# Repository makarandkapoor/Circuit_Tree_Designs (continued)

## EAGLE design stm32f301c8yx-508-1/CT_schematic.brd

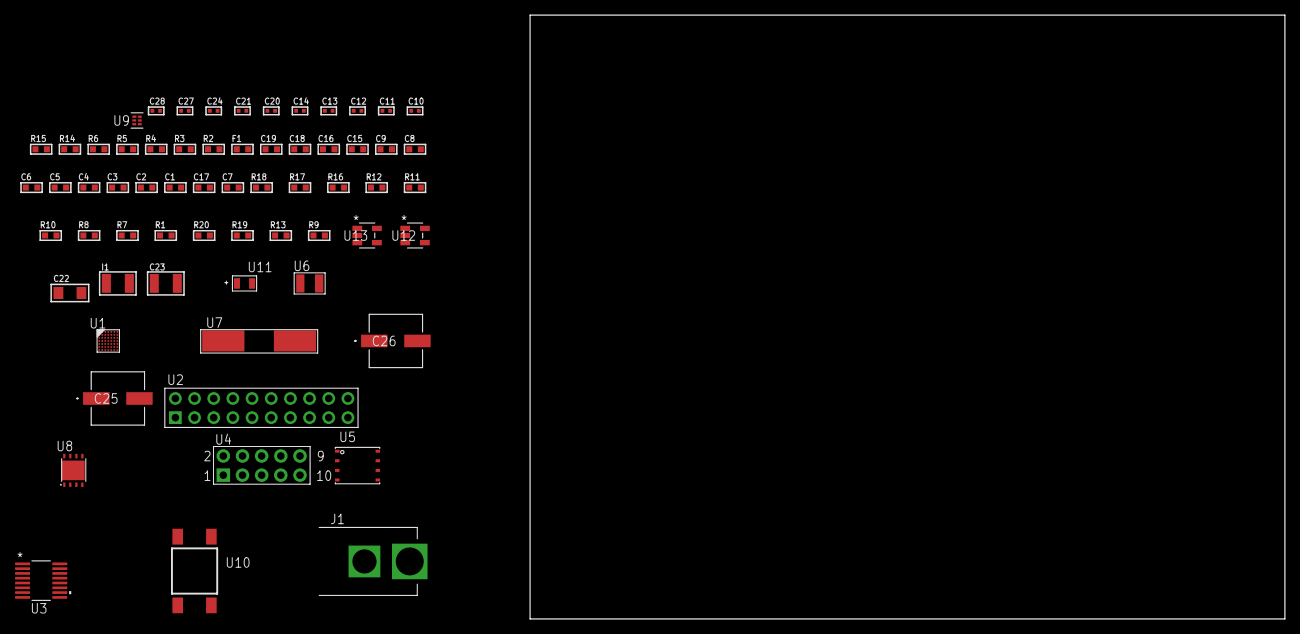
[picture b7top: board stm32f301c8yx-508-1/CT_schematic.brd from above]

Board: 2 copper layers, 100.0 x 80.0 mm, 64 parts (0 on the bottom side), 41 nets, no tracks yet.

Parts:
C1, C9, C15, C16, C18, C19: 1e-06; C0603
C2, C3, C4, C5, C6: 1e-07; C0603
C7: 4.7e-06; C0603
C8: 1e-08; C0603
C10, C11, C12, C13: 1e-11; C0402
C14, C24: 1e-07; C0402
C17: 2.2e-07; C0603
C20, C21, C27, C28: 1e-08; C0402
C22: 1e-05; C1206
C23: 1e-05; C1210
C25, C26: 0.0001; EXV-9H
F1: 240.0; L0603
I1: 1e-05; L1210
J1: PJ-037B; PJ-037B_PACKAGE
R1, R7, R8, R10, R11, R12, R16, R17: 10000.0; R0603
R2, R15: 1000.0; R0603
R3: 1270.0; R0603
R4: 4700.0; R0603
R5, R6: 2200.0; R0603
R9, R13: 100000.0; R0603
R14: 1500.0; R0603
R18: 18000.0; R0603
R19: 470000.0; R0603
R20: 120000.0; R0603
U1: STM32F301C8Y6; WLCSP49
U2: TST-110-05-T-D-RA
U3: LTC2804CGN-1#PBF; SSOP-16
U4: HTSS-105-01-G-D
U5: 24AA256-I/MF; DFN8-S
U6: ABS07-32.768KHZ-7-T
U7: ABLS-25.000MHZ-B2F-T
U8: LP3878SDX-ADJ/NOPB; WSON-8
U9: TPS3895ADRYR; SON-6
U10: 4-1437565-2; SW_4-1437565-2
U11: Q65110A2395; LGM67K-G1J2-24-Z
U12, U13: nc7sz125m5x; NC7SZ125M5X

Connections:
CLK_CRYSTAL_U1_C6: C10.1, U1.C6, U6.1
CLK_CRYSTAL_U1_C7: C11.1, U1.C7, U6.2
CLK_CRYSTAL_U1_D6: C12.1, U1.D6, U7.1
CLK_CRYSTAL_U1_D7: C13.1, U1.D7, U7.2
GND: C1.2, C2.2, C3.2, C4.2, C5.2, C6.2, C7.2, C8.2, C9.2, C10.2, C11.2, C12.2, C13.2, C14.2, C15.2, C16.2, C18.2, C19.2, C20.2, C21.2, C22.2, C23.2, C24.2, C25.2, C26.2, C27.2, C28.2, J1.2, R2.2, R7.2, R15.2, R18.2, R20.2, U1.B1, U1.D3, U1.E6, U1.F7, U2.4, U2.6, U2.8, U2.10, U2.12, U2.14, U2.16, U2.18, U2.20, U3.8, U4.9, U5.4, U8.3, U8.PAD, U9.2, U11.C, U12.2, U12.3, U13.1, U13.3
NET_U1_A2: R5.1, U1.A2, U5.6
NET_U1_A5: R7.1, U1.A5
NET_U1_A6: C8.1, C9.1, F1.1, U1.A6
NET_U1_C5: R6.1, U1.C5, U5.5
NET_U1_E7: R4.1, U1.E7, U13.4
NET_U1_G6: R3.1, U1.G6, U11.A
NET_U1_G7: R1.1, U1.G7, U10.3, U10.4
NET_U3_6: C15.1, U3.6
NET_U3_7: C17.1, I1.2, U3.7
NET_U3_9: C16.1, U3.9
NET_U3_10: C17.2, U3.10
NET_U3_11: R9.1, U3.11
NET_U4_3: U3.1, U4.3
NET_U4_4: U3.2, U4.4
NET_U4_5: U3.3, U4.5
NET_U4_6: U3.4, U4.6
NET_U5_1: R10.1, U5.1
NET_U5_2: R11.1, U5.2
NET_U5_3: R12.1, U5.3
NET_U8_1: C21.1, U8.1
NET_U8_6: R14.2, R15.1, U8.6
NET_U8_8: R13.1, U8.8
NET_U9_1: R17.1, R18.1, U9.1
NET_U9_3: R19.2, R20.1, U9.3
NET_U9_4: R16.1, U9.4, U12.4, U13.2
NET_U10_1: R2.1, U10.1, U10.2
PROC_SYS_JTCK_SWCLK: U1.A1, U2.9
PROC_SYS_JTDO_TRACESWO: U1.A3, U2.13
PROC_SYS_JTMS_SWDIO: U1.B3, U2.7
PROC_USART1_CTS: U1.C1, U3.13
PROC_USART1_RTS: U1.C3, U3.15
PROC_USART1_RX: U1.C2, U3.16
PROC_USART1_TX: U1.C4, U3.14
RST_OUT_U2_SRESET_B: R8.1, U2.15, U12.1
VCC_S1_6V4: C22.1, C25.1, C26.1, J1.1, R13.2, U8.4
VCC_TIER1_2V5: C1.1, C2.1, C3.1, C4.1, C5.1, C6.1, C7.1, C14.1, C18.1, C19.1, C20.1, C23.1, C24.1, C27.1, C28.1, F1.2, I1.1, R1.2, R3.2, R4.2, R5.2, R6.2, R8.2, R9.2, R10.2, R11.2, R12.2, R14.1, R16.2, R17.2, R19.1, U1.B2, U1.B6, U1.B7, U1.F2, U2.1, U3.5, U3.12, U5.7, U5.8, U8.5, U9.6, U12.5, U13.5

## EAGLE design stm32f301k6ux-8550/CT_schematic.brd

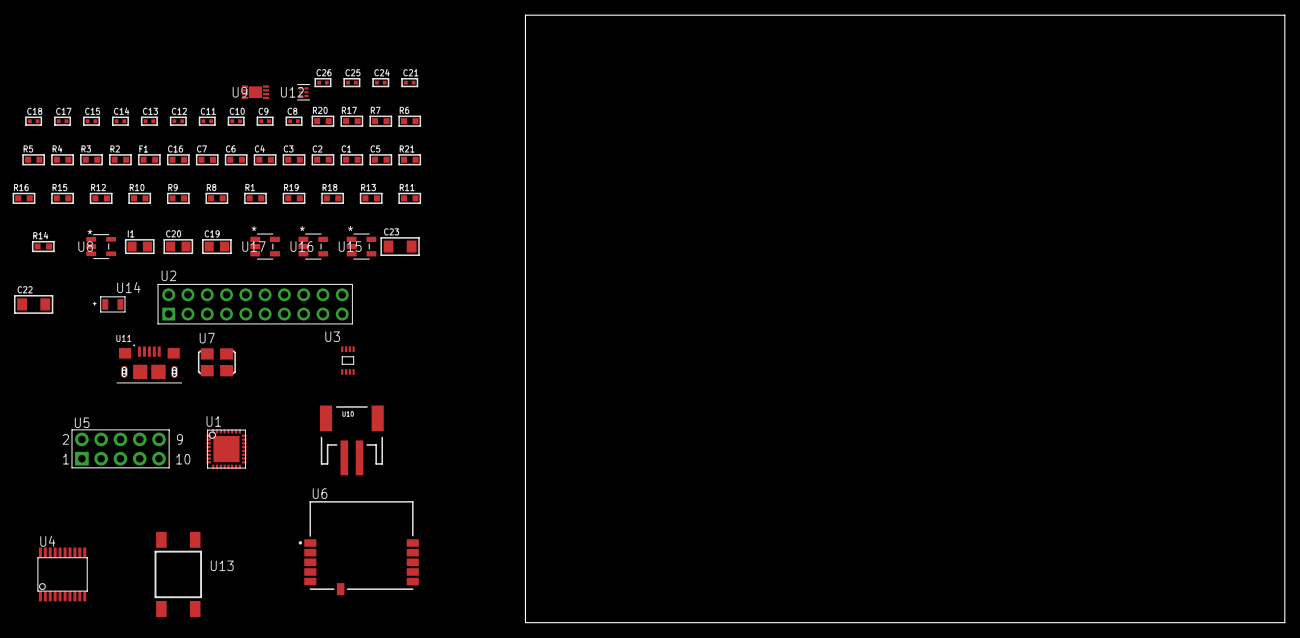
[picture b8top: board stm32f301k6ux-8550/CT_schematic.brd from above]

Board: 2 copper layers, 66 parts (0 on the bottom side), 45 nets, no tracks yet.

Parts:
C1, C2, C3, C4: 1e-07; C0603
C5: 4.7e-06; C0603
C6: 1e-08; C0603
C7, C16: 1e-06; C0603
C8, C10, C11, C12, C13, C14, C15, C17, C21: 1e-07; C0402
C9, C18, C24, C25, C26: 1e-08; C0402
C19, C20: 1e-05; C0805
C22, C23: 1e-05; C1206
F1: 240.0; L0603
I1: 2.2e-06; L0805
R1, R8, R9, R10, R15, R16, R21: 10000.0; R0603
R2: 1000.0; R0603
R3: 1600.5; R0603
R4, R5: 4700.0; R0603
R6, R7: 2200.0; R0603
R11: 100000.0; R0603
R12: 47000.0; R0603
R13: 220000.0; R0603
R14: 1000000.0; R0603
R17: 9100.0; R0603
R18: 680000.0; R0603
R19: 120000.0; R0603
R20: 2000.0; R0603
U1: STM32F301K6U6; UFQFPN32
U2: TST-110-05-T-D-RA
U3: 24AA00T-I/MNY; TDFN-8/6MM
U4: SP3203ECY-L/TR; TSSOP20-I
U5: HTSS-105-01-G-D
U6: SPBTLE-RF; XCVR_SPBTLE-RF
U7: ASFL1-25MHZ-NCS; ASFL1
U8: ltc3406es5; TSOT-23-5
U9: MCP73831T-2ACI/MC; DFN8_2X3MC
U10: S2B-PH-SM4-TB(LF)(SN); JST-2-SMD
U11: 10118193-0001LF; FCI_10118193-0001LF
U12: TPS3895ADRYR; SON-6
U13: 4-1437565-2; SW_4-1437565-2
U14: Q65110A2395; LGM67K-G1J2-24-Z
U15, U16, U17: nc7sz125m5x; NC7SZ125M5X

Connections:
CLK_U1_2: U1.2, U7.3
GND: C1.2, C2.2, C3.2, C4.2, C5.2, C6.2, C7.2, C8.2, C9.2, C10.2, C11.2, C14.2, C15.2, C16.2, C17.2, C18.2, C19.2, C20.1, C20.2, C21.2, C22.2, C23.2, C24.2, C25.2, C26.2, R2.2, R8.2, R11.2, R12.2, R13.2, R17.2, R19.2, R20.2, U1.6, U1.16, U1.32, U1.EPAD, U2.4, U2.6, U2.8, U2.10, U2.12, U2.14, U2.16, U2.18, U2.20, U3.4, U4.18, U5.9, U6.6, U7.2, U8.2, U9.6, U9.9, U10.2, U11.5, U11.6, U11.7, U11.8, U11.9, U12.2, U14.C, U15.2, U15.3, U16.1, U16.3, U17.1, U17.3
INPUT_USBPOWER_5V: C22.1, R21.2, U9.1, U9.2, U11.1
NET_U1_4: R5.1, U1.4, U17.4
NET_U1_5: C6.1, C7.1, F1.1, U1.5
NET_U1_25: R6.1, U1.25, U3.6
NET_U1_28: R3.1, U1.28, U14.A
NET_U1_29: R1.1, U1.29, U13.3, U13.4
NET_U1_30: R7.1, U1.30, U3.5
NET_U1_31: R8.1, U1.31
NET_U4_1: C12.1, U4.1
NET_U4_2: C14.1, U4.2
NET_U4_3: C12.2, U4.3
NET_U4_4: C13.1, U4.4
NET_U4_5: C13.2, U4.5
NET_U4_6: C15.1, U4.6
NET_U5_3: U4.14, U5.3
NET_U5_4: U4.13, U5.4
NET_U5_5: U4.17, U5.5
NET_U5_6: U4.16, U5.6
NET_U6_10: R10.1, U6.10
NET_U6_11: R4.1, U6.11, U16.4
NET_U8_3: I1.1, U8.3
NET_U8_5: R13.1, R14.1, U8.5
NET_U8_ATNET_3: I1.2, R14.2
NET_U9_5: R21.1, U9.5
NET_U9_8: R20.1, U9.8
NET_U12_1: R16.1, R17.1, U12.1
NET_U12_3: R18.2, R19.1, U12.3
NET_U12_4: R15.1, U12.4, U15.4, U16.2, U17.2
NET_U13_1: R2.1, U13.1, U13.2
PROC_GPIO_TO_U6_SPI_IRQ: R12.1, U1.11, U6.4
PROC_SPI2_MISO: U1.20, U6.8
PROC_SPI2_MOSI: U1.21, U6.9
PROC_SPI2_SCK: R11.1, U1.3, U6.7
PROC_SYS_JTCK_SWCLK: U1.24, U2.9
PROC_SYS_JTDO_TRACESWO: U1.26, U2.13
PROC_SYS_JTMS_SWDIO: U1.23, U2.7
PROC_USART2_CTS: U1.7, U4.8
PROC_USART2_RTS: U1.8, U4.10
PROC_USART2_RX: U1.10, U4.11
PROC_USART2_TX: U1.9, U4.7
RST_OUT_U2_SRESET_B: R9.1, U2.15, U15.1
VCC_S1_3V7: C19.1, C23.1, U8.4, U9.3, U9.4, U10.1
VCC_TIER1_3V3: C1.1, C2.1, C3.1, C4.1, C5.1, C8.1, C9.1, C10.1, C11.1, C16.1, C17.1, C18.1, C20.2, C21.1, C24.1, C25.1, C26.1, F1.2, I1.2, R1.2, R3.2, R4.2, R5.2, R6.2, R7.2, R9.2, R10.2, R14.2, R15.2, R16.2, R18.1, U1.1, U1.17, U2.1, U3.8, U4.12, U4.19, U6.5, U7.4, U12.6, U15.5, U16.5, U17.5
